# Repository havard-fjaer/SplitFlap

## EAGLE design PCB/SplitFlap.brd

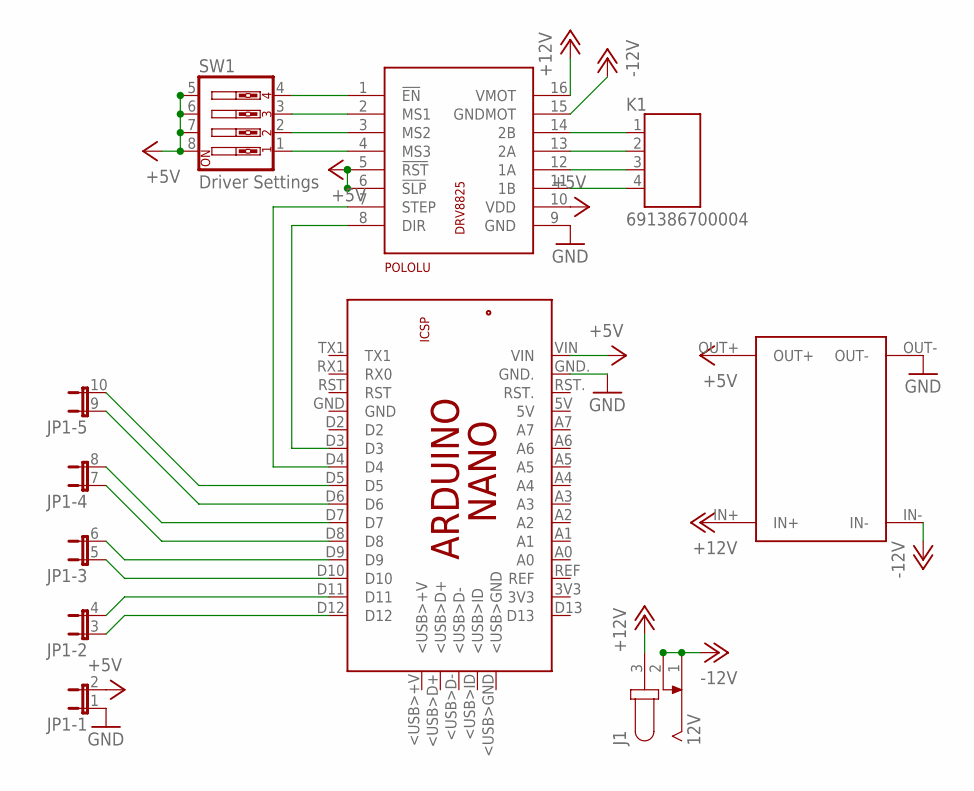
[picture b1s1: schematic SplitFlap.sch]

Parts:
J1: 12V; SPC4077
JP1: JP5QE; JP5Q
K1: 691386700004
LEIVIN: LEIVIN_PWR
PCB1: ARDUINO_NANO
POLOLU: DRV8825; DIP16
SW1: Driver Settings; EDG-04

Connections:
+5V: JP1.2, LEIVIN.OUT+, PCB1.VIN, POLOLU.5 (!RST!), POLOLU.6 (!SLP!), POLOLU.10 (VDD), SW1.5, SW1.6, SW1.7, SW1.8
+12V: J1.3, LEIVIN.IN+, POLOLU.16 (VMOT)
-12V: J1.1, J1.2, LEIVIN.IN-, POLOLU.15 (GNDMOT)
GND: JP1.1, LEIVIN.OUT-, PCB1.GND., POLOLU.9 (GND)
unnamed: POLOLU.1 (!EN!), SW1.4
unnamed: POLOLU.2 (MS1), SW1.3
unnamed: POLOLU.3 (MS2), SW1.2
unnamed: POLOLU.4 (MS3), SW1.1
unnamed: PCB1.D3, POLOLU.8 (DIR)
unnamed: PCB1.D4, POLOLU.7 (STEP)
unnamed: K1.1, POLOLU.14 (2B)
unnamed: K1.2, POLOLU.13 (2A)
unnamed: K1.3, POLOLU.12 (1A)
unnamed: K1.4, POLOLU.11 (1B)
unnamed: JP1.10 (2), PCB1.D5
unnamed: JP1.9 (1), PCB1.D6
unnamed: JP1.8 (2), PCB1.D7
unnamed: JP1.7 (1), PCB1.D8
unnamed: JP1.6 (2), PCB1.D9
unnamed: JP1.5 (1), PCB1.D10
unnamed: JP1.4 (2), PCB1.D11
unnamed: JP1.3 (1), PCB1.D12

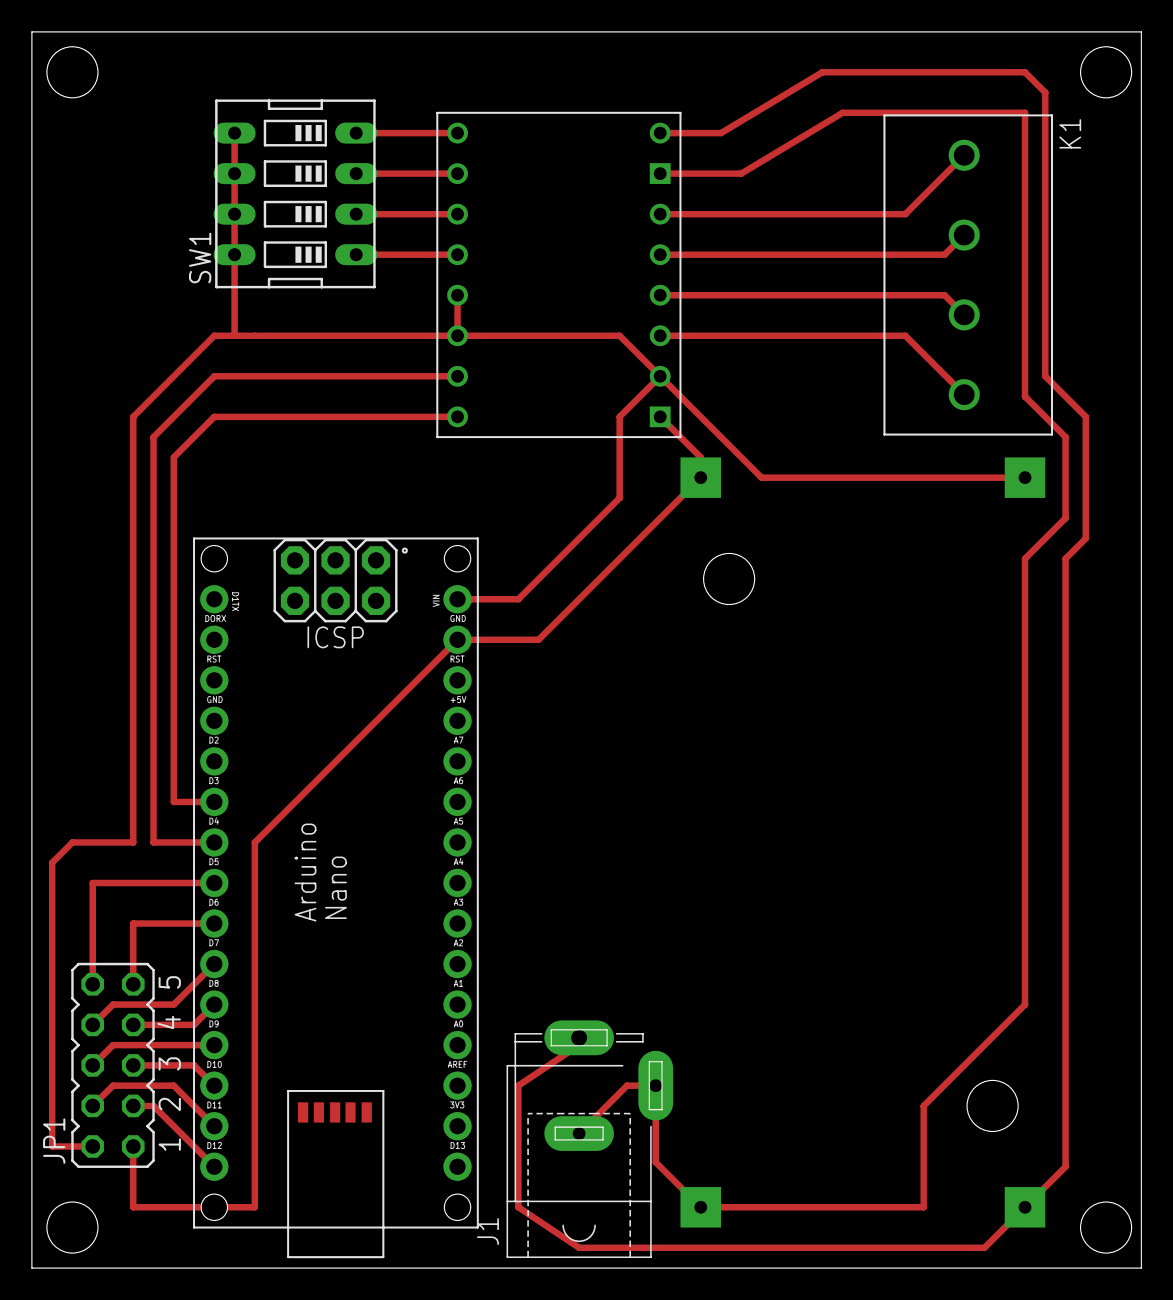
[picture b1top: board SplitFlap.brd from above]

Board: 2 copper layers, 69.5 x 77.5 mm, 7 parts (1 on the bottom side), 22 nets.

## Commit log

2015-10-11 Initial commit. Keeping experimental files.
2015-10-11 Added gulp
2015-10-11 Splitting out features
2015-10-11 Defining requirements, adapting gulp for Mac
2015-10-11 Ignoring modules
2015-10-11 Implementing stepper logic, and moving LCD logic.
2015-10-11 Fixed string bug
2015-10-11 Ignore
2015-10-11 Fixed undefined bug, added callback to calibration.
2015-10-11 Incremented version
2015-10-11 Switched to 1 based position system, instead of zero based.
2015-10-11 Tightened input validation
2015-10-12 Removed .idea
2015-10-12 Ignore .idea
2015-11-03 New pi ip
2015-11-03 Updated pins
2015-11-12 Index.html
2015-11-17 Added Eagle Schematics

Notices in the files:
parts and their libraries:
Wurth_Elektronik_Electromechanic_Termina: Copyright: Würth Elektronik
